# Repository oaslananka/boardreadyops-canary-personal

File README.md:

# boardreadyops-canary-personal
BoardReadyOps synthetic secondary-installation target-repository canary

Visibility authorization check: this repository was temporarily made private to verify that a
signed-in owner can read its run while an anonymous visitor cannot.

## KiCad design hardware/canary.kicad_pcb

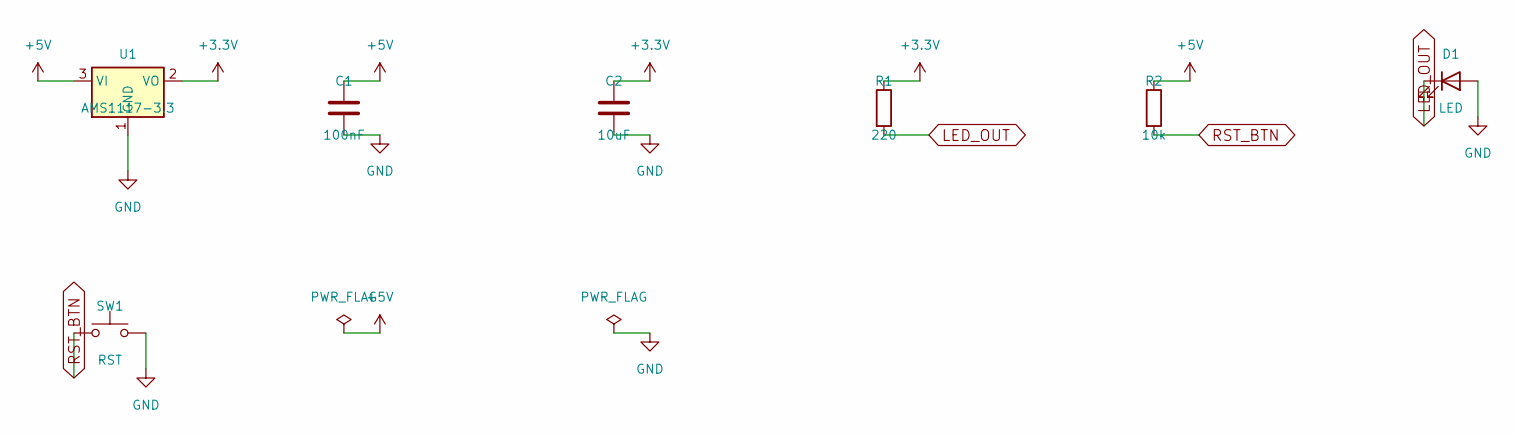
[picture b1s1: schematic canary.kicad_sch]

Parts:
C1: 100nF; C_1206_3216Metric
C2: 10uF; C_1206_3216Metric
D1: LED; LED_1206_3216Metric
R1: 220; R_1206_3216Metric
R2: 10k; R_1206_3216Metric
SW1: RST; SW_SPST_PTS810
U1: AMS1117-3.3; SOT-223-3_TabPin2

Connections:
+3.3V: C2.1, R1.1, U1.2 (VO)
+5V: C1.1, R2.1, U1.3 (VI)
GND: C1.2, C2.2, D1.2 (A), SW1.2, U1.1 (GND)
LED_OUT: D1.1 (K), R1.2
RST_BTN: R2.2, SW1.1

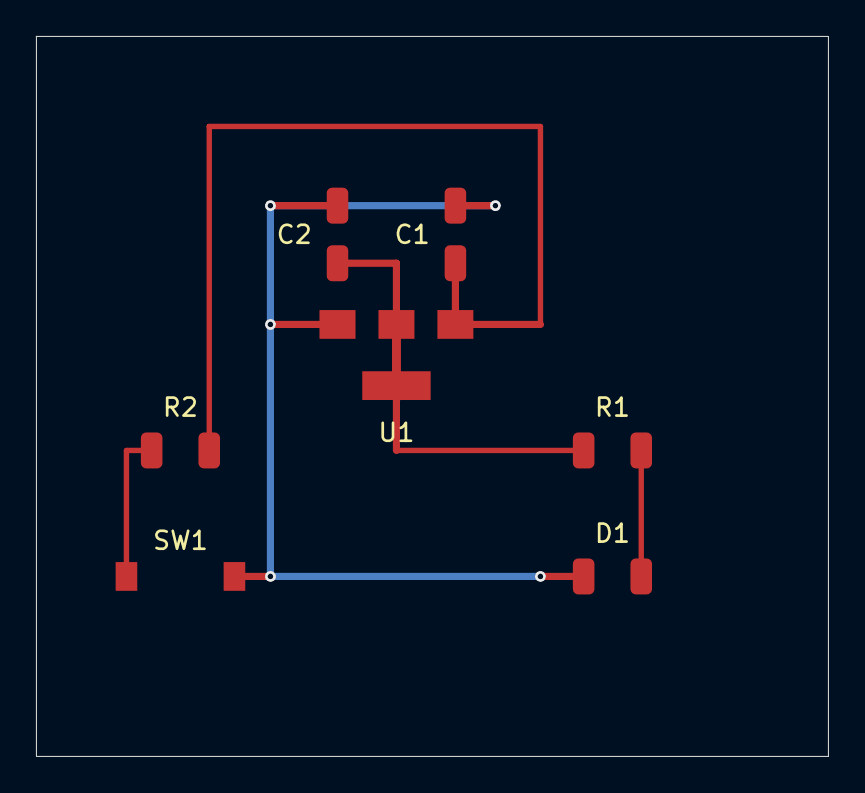
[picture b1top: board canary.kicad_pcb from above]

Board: 2 copper layers, 44.0 x 40.0 mm, 7 parts (0 on the bottom side), 5 nets.

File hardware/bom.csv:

Reference,Value,Footprint,Manufacturer,MPN,Supplier,RoHS,Lifecycle,Notes
U1,AMS1117-3.3,Package_TO_SOT_SMD:SOT-223-3_TabPin2,AMS,AMS1117-3.3,"Digi-Key, Mouser, LCSC",Compliant,Active,5V to 3.3V LDO Regulator
R1,220,Resistor_SMD:R_1206_3216Metric,"Yageo, Bourns","RC1206FR-07220RL","Digi-Key, Mouser",Compliant,Active,LED current limiting resistor
R2,10k,Resistor_SMD:R_1206_3216Metric,"Yageo, Bourns","RC1206FR-0710KL","Digi-Key, Mouser",Compliant,Active,Reset pull-up resistor
C1,100nF,Capacitor_SMD:C_1206_3216Metric,"Murata, Samsung","GRM31CR61H104KA88L","Digi-Key, Mouser",Compliant,Active,Input decoupling capacitor
C2,10uF,Capacitor_SMD:C_1206_3216Metric,"Samsung, Murata","CL10A106MA8NRNC","Digi-Key, Mouser",Compliant,Active,Output bulk capacitor
D1,LED,LED_SMD:LED_1206_3216Metric,"Osram, Broadcom","LY R976-PS-35","Digi-Key, Mouser",Compliant,Active,Green LED indicator (635nm)
SW1,RST,Button_Switch_SMD:SW_SPST_PTS810,"C&K Components","PTS810 SJM 250 SMTR LFS","Digi-Key, Mouser",Compliant,Active,Reset/Test push button
